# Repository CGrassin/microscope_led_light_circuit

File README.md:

# Microscope LED Driver circuit

This circuit drives a 1W or 3W LED to convert old optical microscopes from light bulb/halogen lamp to LED ligthing.

It is powered from a USB type C port and is fully dimmable. It may be used with a USB power bank, for instance.

LEDs are considerably more efficient (i.e. less heat), have a longer lifespan and have a better color accuracy than bulbs. My circuit has a high PWM frequency to avoid flickering and rolling bands effect in photographs.

## Features

| Specification  | Value                                     |
|:---------------|:------------------------------------------|
| Power input    | 5V @ 1A max. (USB type C)                 |
| PWM frequency  | >8KHz                                     |
| Controls       | Combined knob dimming (0-100%) and ON/OFF |
| Estimated cost | About $10                                 |

## Build instructions

Gerber files are ready to upload to your prefered PCB manufacturer. The components are generic and should be available at most electronic components distributors. I personally use JLCPCB and LCSC.

Hand soldering this board is easy. I included an "interactive BOM" to help with part placement.

The only additional required parts are a 1W or 3W "star" LED with a 30° lens to pre-focus the light into the condenser. Thank to this lens, a 1W LED is sufficient. You can choose your favorite color temperature.

I also included a 3D-printable case for the circuit. Print at 0.2mm layer height, no support required.

*Although I designed a PCB, this circuit could be build on a piece of stripboard or even breadboard.*

## Principle of operation

This circuit uses a classic 555 variable duty cycle astable multivibrator configuration.

The potentiometer adjusts the charge and discharge rate of the TRIG capacitor. The frequency of the carrier depend on the RC constant of those parts.

## License

All files in this repository are released under CC-BY license.

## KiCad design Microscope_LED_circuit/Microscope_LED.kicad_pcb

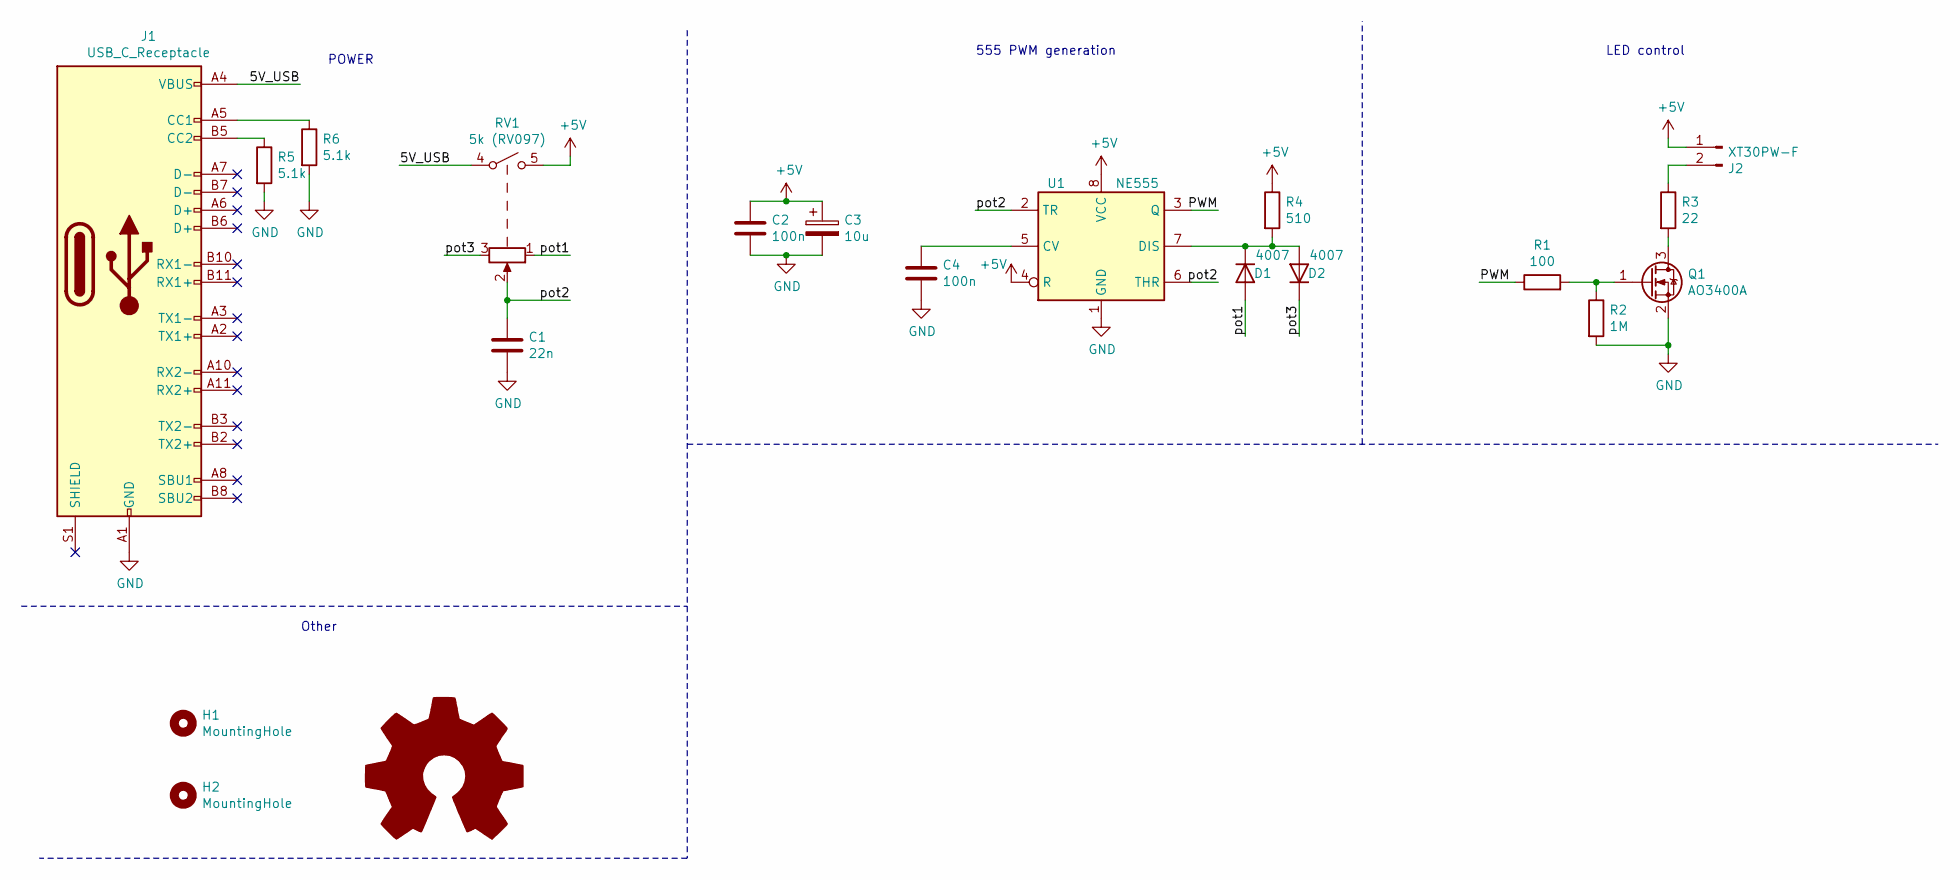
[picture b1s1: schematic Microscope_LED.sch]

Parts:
C1: 22n; C_0805_2012Metric_Pad1.15x1.40mm_HandSolder; LCSC C282752
C2, C4: 100n; C_0805_2012Metric_Pad1.15x1.40mm_HandSolder; LCSC C476766
C3: 10u; CP_Elec_5x5.4; LCSC C72487
D1, D2: 4007; D_SOD-123F; LCSC C108803
H1, H2: MountingHole; MountingHole_3.2mm_M3
J1: USB_C_Receptacle; USB_C_Receptacle_HRO_TYPE-C-31-M-12; LCSC C393939
J2: XT30PW-F; PhoenixContact_MC_1,5_2-G-3.81_1x02_P3.81mm_Horizontal; LCSC C8387
LOGO1: Logo_Open_Hardware_Large; Charleslabs_Logo_5mm
Q1: AO3400A; SOT-23; LCSC C122850
R1: 100; R_0805_2012Metric_Pad1.15x1.40mm_HandSolder; LCSC C17408
R2: 1M; R_0805_2012Metric_Pad1.15x1.40mm_HandSolder; LCSC C17514
R3: 22; R_1206_3216Metric
R4: 510; R_0805_2012Metric_Pad1.15x1.40mm_HandSolder; LCSC C25317
R5, R6: 5.1k; R_0805_2012Metric_Pad1.15x1.40mm_HandSolder; LCSC C115337
RV1: 5k (RV097); RV097
U1: NE555; SOIC-8_3.9x4.9mm_P1.27mm; LCSC C7593

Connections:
+5V: C2.1, C3.1, J2.1, R4.1, RV1.5, U1.4 (R), U1.8 (VCC)
/5V_USB: J1.A4 (VBUS), J1.A9 (VBUS), J1.B4 (VBUS), J1.B9 (VBUS), RV1.4
/PWM: R1.1, U1.3 (Q)
/pot1: D1.2 (A), RV1.1
/pot2: C1.1, RV1.2, U1.2 (TR), U1.6 (THR)
/pot3: D2.1 (K), RV1.3
GND: C1.2, C2.2, C3.2, C4.2, J1.A1 (GND), J1.A12 (GND), J1.B1 (GND), J1.B12 (GND), Q1.2 (S), R2.2, R5.2, R6.2, U1.1 (GND)
unnamed: C4.1, U1.5 (CV)
unnamed: D1.1 (K), D2.2 (A), R4.2, U1.7 (DIS)
unnamed: J1.A5 (CC1), R6.1
unnamed: J1.B5 (CC2), R5.1
unnamed: J2.2, R3.1
unnamed: Q1.1 (G), R1.2, R2.1
unnamed: Q1.3 (D), R3.2

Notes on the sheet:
POWER
555 PWM generation
LED control
Other

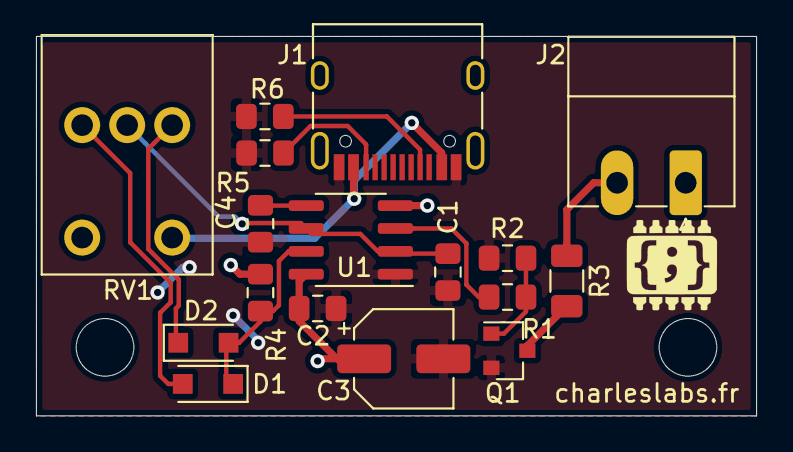
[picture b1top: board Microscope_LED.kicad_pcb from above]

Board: 2 copper layers, 40.0 x 21.1 mm, 20 parts (0 on the bottom side), 14 nets.

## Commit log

2020-11-17 Release PCB rev. 1
2020-11-17 Release PCB rev. 2
2023-03-06 Create LICENSE
